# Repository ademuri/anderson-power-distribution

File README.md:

# Anderson power distribution

This is PCB designs for power distribution boards that use Anderson PowerPole 45-amp connectors.

See the board-to-wire connector [drawings](https://www.andersonpower.com/content/dam/app/ecommerce/product-pdfs/PP1545/b02021s.pdf). These designs use the `1335G1` (straight) and `1336G1` (right-angle) parts.

"This is not an officially supported Google product"

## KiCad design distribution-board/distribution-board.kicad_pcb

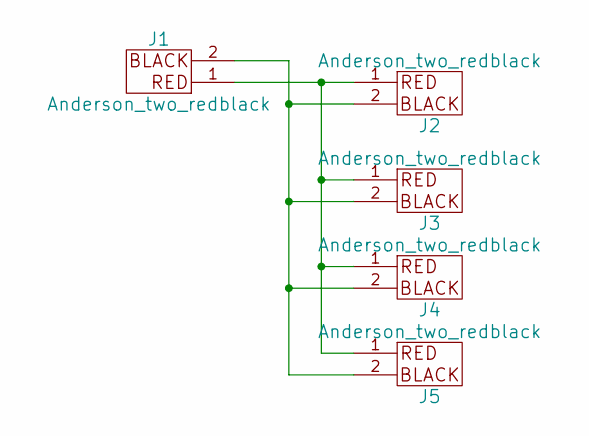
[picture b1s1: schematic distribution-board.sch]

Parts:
J1: Anderson_two_redblack; Anderson_1336G1_right_angle_bottom_two
J2, J3, J4, J5: Anderson_two_redblack; Anderson_1335G1_straight_two

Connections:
unnamed: J1.1, J2.1, J3.1, J4.1, J5.1
unnamed: J1.2, J2.2, J3.2, J4.2, J5.2

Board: 2 copper layers, 5 parts (0 on the bottom side), 2 nets, no tracks yet.

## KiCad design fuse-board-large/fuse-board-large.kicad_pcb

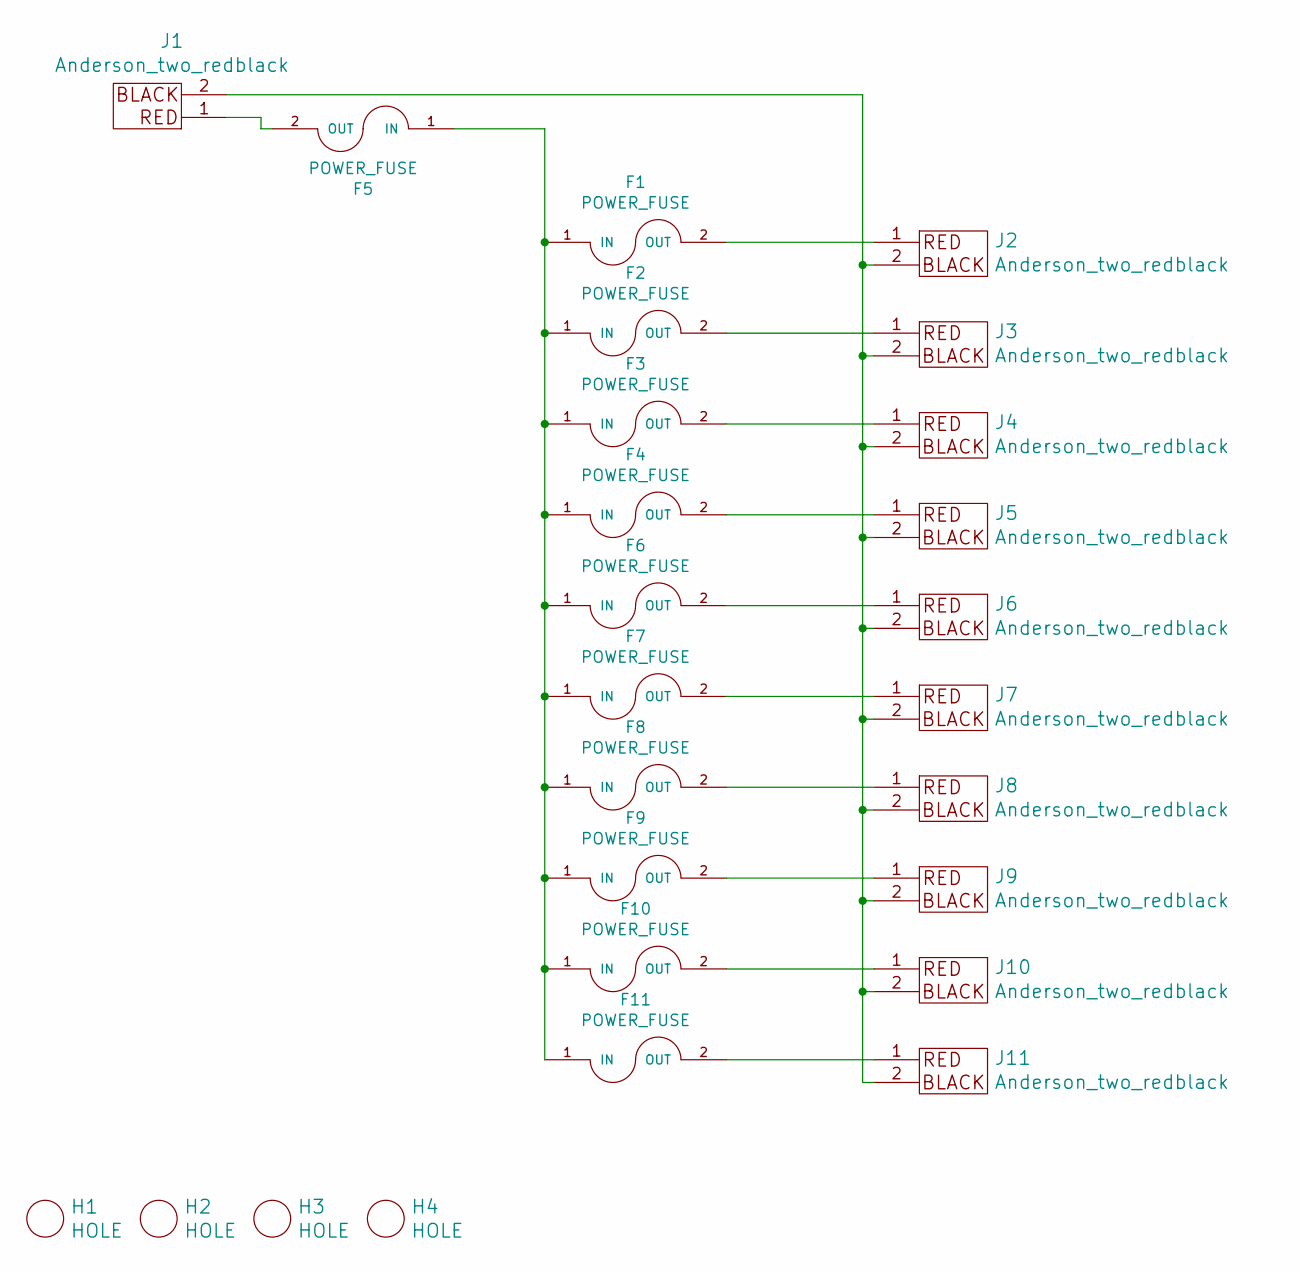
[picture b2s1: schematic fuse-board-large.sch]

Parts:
F1, F2, F3, F4, F5, F6, F7, F8, F9, F10, F11: POWER_FUSE; FUSEHOLDER_ATC_Bk-6010
H1, H2, H3, H4: HOLE; HOLE_5MM_#8
J1: Anderson_two_redblack; Anderson_1336G1_right_angle_bottom_two
J2, J3, J4, J5, J6, J7, J8, J9, J10, J11: Anderson_two_redblack; Anderson_1335G1_straight_two

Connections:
unnamed: F1.1 (IN), F2.1 (IN), F3.1 (IN), F4.1 (IN), F5.1 (IN), F6.1 (IN), F7.1 (IN), F8.1 (IN), F9.1 (IN), F10.1 (IN), F11.1 (IN)
unnamed: F1.2 (OUT), J2.1
unnamed: F2.2 (OUT), J3.1
unnamed: F3.2 (OUT), J4.1
unnamed: F4.2 (OUT), J5.1
unnamed: F5.2 (OUT), J1.1
unnamed: F6.2 (OUT), J6.1
unnamed: F7.2 (OUT), J7.1
unnamed: F8.2 (OUT), J8.1
unnamed: F9.2 (OUT), J9.1
unnamed: F10.2 (OUT), J10.1
unnamed: F11.2 (OUT), J11.1
unnamed: J1.2, J2.2, J3.2, J4.2, J5.2, J6.2, J7.2, J8.2, J9.2, J10.2, J11.2

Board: 2 copper layers, 26 parts (0 on the bottom side), 13 nets, no tracks yet.

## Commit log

2020-02-25 Hardware v1.0:
    - Tested and works
    - Silk for Anderson connectors is off
2020-02-25 Hardware v1.1:
    - Fix silk outline of Anderson connectors
    - Switch to standard ATC fuse holder
    - Add thermal relief
2020-02-25 Distribution board v1.1:
    - Fix silk on anderson connectors
2020-02-25 Add distribution board v1.0:
    - Silkscreen is way off
    - ..but board works fine
2020-02-25 Move fuse board to subdirectory
2020-02-26 Rename fuse-board to fuse-board-small
2020-02-28 Add a large fuse board with 10 positions
2020-03-15 fuse-board-large v1.1:
    - Update straight Anderson footprint for fixed silk, bigger copper ring
2020-03-21 fuse-board-small v1.1:
    - Update straight Anderson footprint for fixed silk, bigger copper ring
2020-03-21 distribution-board v1.2:
    - Update straight Anderson footprint for fixed silk, bigger copper ring
2020-03-21 Rename KiCAD files to match board names
2020-03-21 Add contributing and license
